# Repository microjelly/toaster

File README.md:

# toaster
A barebones toaster reflow board and software. For details please visit my [project log](https://microjelly.com/reflow-controller-replacement/)

## Software
### Build
This project currently is using a Docker based build system. 
\
\
*from a command line*
```bash
git clone https://github.com/microjelly/toaster.git
cd toaster/build
make sdcc/stm8s-ebake1.ihx
make sdcc/n76e003-ebake1.ihx
```
`stm8s-ebake1.ihx` and `n76e003-ebake1.ihx` will be found in the `build/bin` directory. 

### Flash STM8s
https://github.com/vdudouyt/stm8flash
```bash
stm8flash -c stlinkv2 -p stm8s103?3 -w stm8s-ebake1.ihx
```

### Flash N76E003
https://github.com/erincandescent/nuvoprog
```bash
nuvoprog program -t n76e003 -c FFFFFFFF -a n76e003-bake1.ihx
```

## Hardware
`hw/v1/bom/index.html` has component value and placement information.

### STM8s build
Reference | Value
-- | --
C5 | 1uF
R5 | DNP (Do Not Populate)
U1 | STM8S103F3P6

### N76E003 build
Reference | Value
-- | --
C5 | DNP (Do Not Populate)
R5 | 0 Ohm
U1 | N76E003AT20

### Programing/Debug Header
The header uses a 10pin card edge 2.54mm pitch connector.
```
Top with pads on the bottom right
 | 2| 4| 6| 8|10|

Bottom with pads on the bottom left
 | 1| 3| 5| 7| 9|
```

Pad | STM8s | N76E003
-- | -- | --
1 | 3v3 | 3v3
2 | 3v3 | 3v3
3 | GND | GND
4 | SWIM | ICPCK
5 | GND | GND
6 | GND | GND
7 | RX | RX
8 | NRST | RST
9 | TX | TX
10 | N/A | ICPDAT

## Debug
Connect RX/TX/GND to a serial device.
\
\
OSX; (exit Ctrl+A; Ctrl+\\; Y)
```bash
screen -port /dev/tty.usbserial-0001 115200
```

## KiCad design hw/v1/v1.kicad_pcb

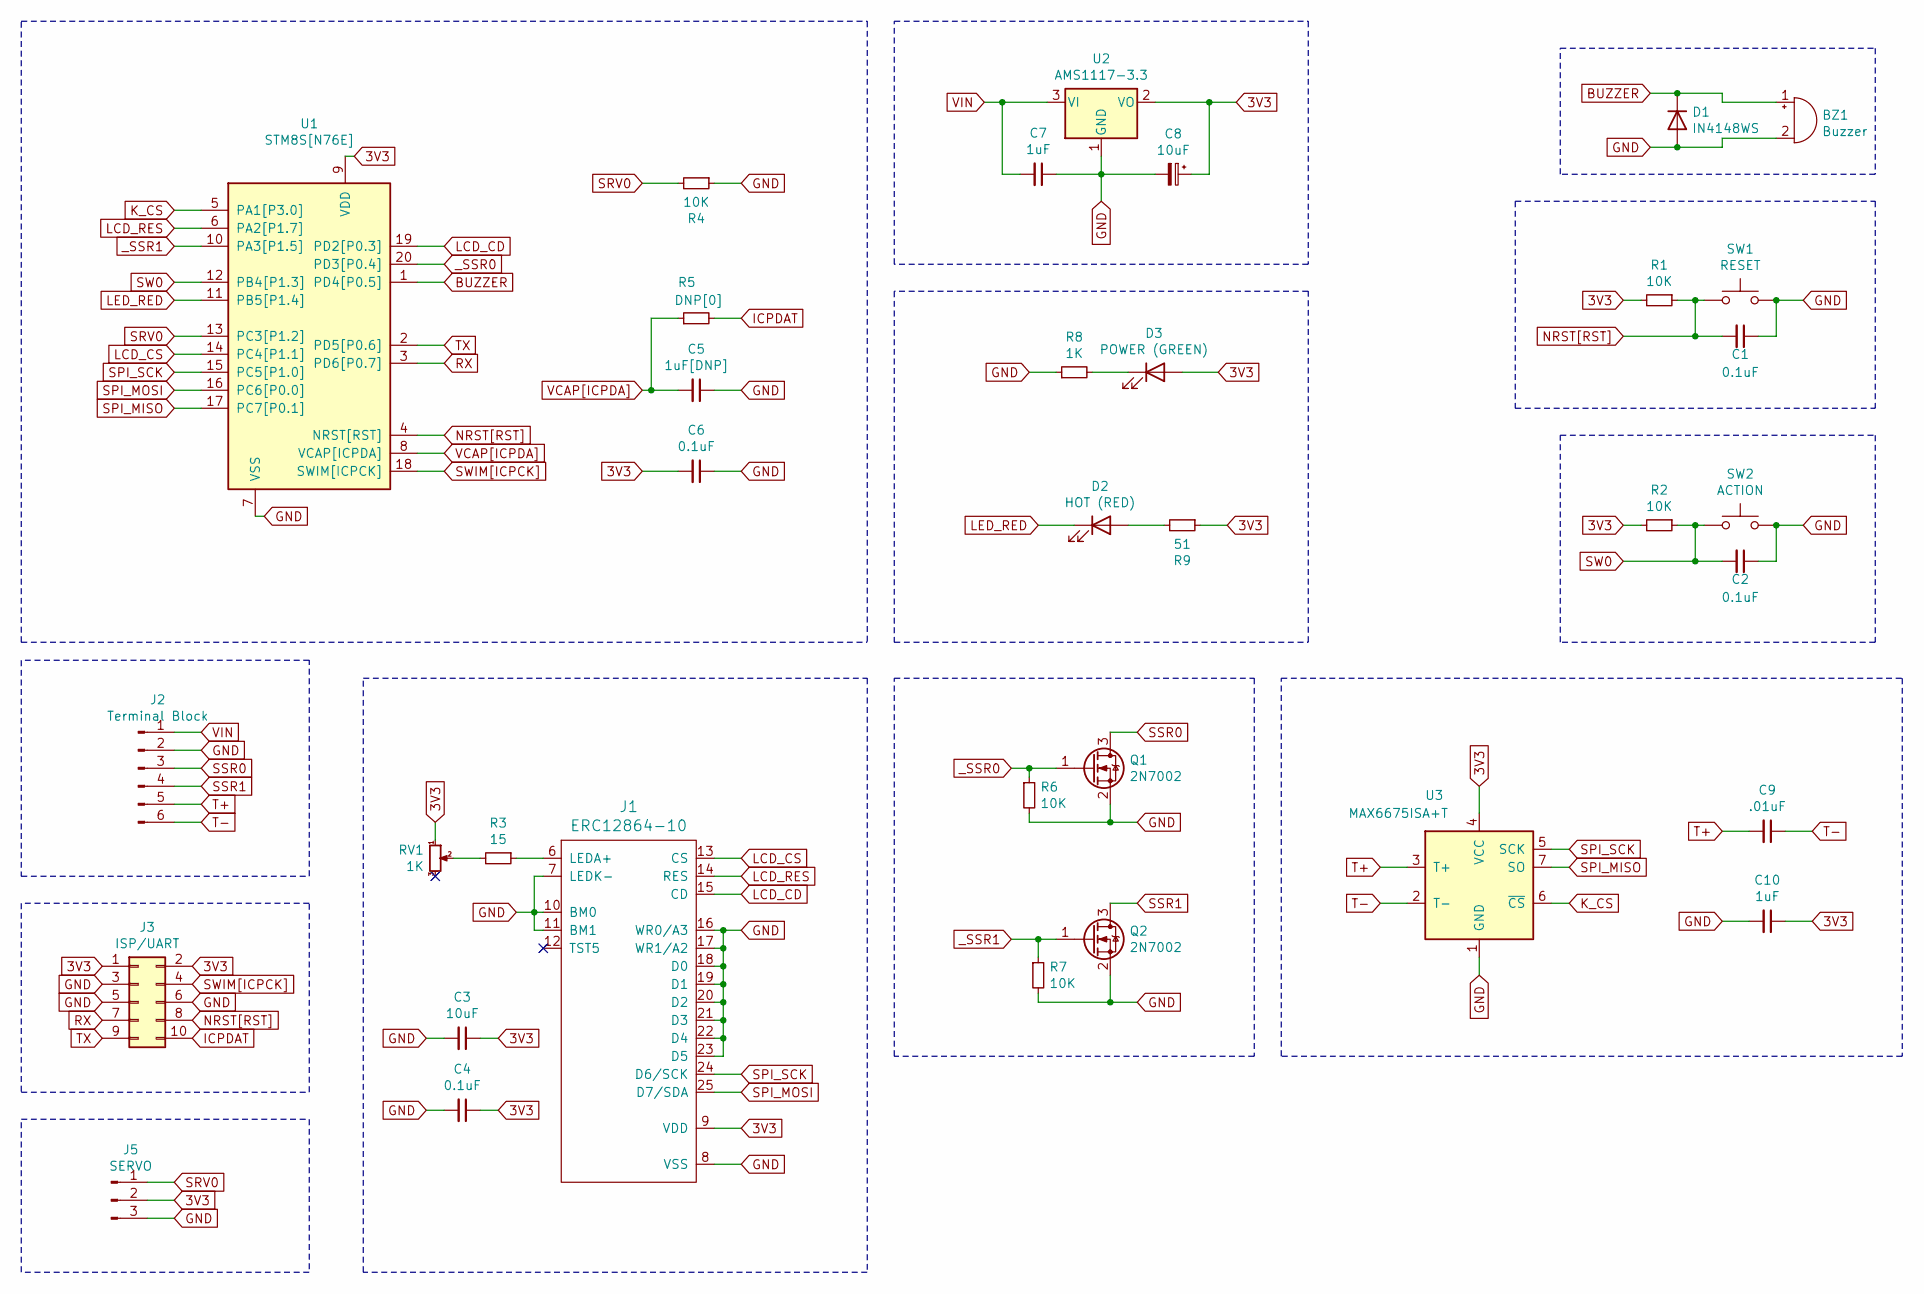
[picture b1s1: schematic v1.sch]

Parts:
BZ1: Buzzer; MLT-8530
C1, C2, C4, C6: 0.1uF; C_0805_2012Metric
C3: 10uF; C_0805_2012Metric
C5: 1uF[DNP]; C_0805_2012Metric
C7, C10: 1uF; C_0805_2012Metric
C8: 10uF; CP_EIA-3216-18_Kemet-A
C9: .01uF; C_0805_2012Metric
D1: IN4148WS; D_SOD-323
D2: HOT (RED); LED_0805_2012Metric
D3: POWER (GREEN); LED_0805_2012Metric
J1: ERC12864-10; ER-CON30HB-1
J2: Terminal Block; HT396V-3.96-6p
J3: ISP/UART; TRUDEAU_C2X5_SMD
J5: SERVO; PinHeader_1x03_P2.54mm_Vertical
Q1, Q2: 2N7002; SOT-23
R1, R2, R4, R6, R7: 10K; R_0805_2012Metric
R3: 15; R_0805_2012Metric
R5: DNP[0]; R_0805_2012Metric
R8: 1K; R_0805_2012Metric
R9: 51; R_0805_2012Metric
RV1: 1K; Potentiometer_Bourns_TC33X_Vertical
SW1: RESET; TS-1186D-C-A
SW2: ACTION; UK-B0229-G2.5-B-250
U1: STM8S[N76E]; TSSOP-20_4.4x6.5mm_P0.65mm
U2: AMS1117-3.3; SOT-223-3_TabPin2
U3: MAX6675ISA+T; SOIC-8_3.9x4.9mm_P1.27mm

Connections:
3V3: C3.1, C4.1, C6.2, C8.1, C10.1, D3.2 (A), J1.9 (VDD), J3.1, J3.2, J5.2, R1.2, R2.2, R9.1, RV1.1, U1.9 (VDD), U2.2 (VO), U3.4 (VCC)
BUZZER: BZ1.1 (-), D1.1 (K), U1.1 (PD4[P0.5])
GND: BZ1.2 (+), C1.1, C2.1, C3.2, C4.2, C5.1, C6.1, C7.1, C8.2, C10.2, D1.2 (A), J1.7 (LEDK-), J1.8 (VSS), J1.10 (BM0), J1.11 (BM1), J1.16 (WR0/A3), J1.17 (WR1/A2), J1.18 (D0), J1.19 (D1), J1.20 (D2), J1.21 (D3), J1.22 (D4), J1.23 (D5), J2.2, J3.3, J3.5, J3.6, J5.3, Q1.2 (S), Q2.2 (S), R4.1, R6.2, R7.2, R8.1, SW1.2, SW2.2, U1.7 (VSS), U2.1 (GND), U3.1 (GND)
ICPDAT: J3.10, R5.2
K_CS: U1.5 (PA1[P3.0]), U3.6 (~CS~)
LCD_CD: J1.15 (CD), U1.19 (PD2[P0.3])
LCD_CS: J1.13 (CS), U1.14 (PC4[P1.1])
LCD_RES: J1.14 (RES), U1.6 (PA2[P1.7])
LED_RED: D2.1 (K), U1.11 (PB5[P1.4])
NRST[RST]: C1.2, J3.8, R1.1, SW1.1, U1.4 (NRST[RST])
unnamed: D2.2 (A), R9.2
unnamed: D3.1 (K), R8.2
unnamed: J1.6 (LEDA+), R3.1
unnamed: R3.2, RV1.2
RX: J3.7, U1.3 (PD6[P0.7])
SPI_MISO: U1.17 (PC7[P0.1]), U3.7 (SO)
SPI_MOSI: J1.25 (D7/SDA), U1.16 (PC6[P0.0])
SPI_SCK: J1.24 (D6/SCK), U1.15 (PC5[P1.0]), U3.5 (SCK)
SRV0: J5.1, R4.2, U1.13 (PC3[P1.2])
SSR0: J2.3, Q1.3 (D)
SSR1: J2.4, Q2.3 (D)
SW0: C2.2, R2.1, SW2.1, U1.12 (PB4[P1.3])
SWIM[ICPCK]: J3.4, U1.18 (SWIM[ICPCK])
T+: C9.2, J2.5, U3.3 (T+)
T-: C9.1, J2.6, U3.2 (T-)
TX: J3.9, U1.2 (PD5[P0.6])
VCAP[ICPDA]: C5.2, R5.1, U1.8 (VCAP[ICPDA])
VIN: C7.2, J2.1, U2.3 (VI)
_SSR0: Q1.1 (G), R6.1, U1.20 (PD3[P0.4])
_SSR1: Q2.1 (G), R7.1, U1.10 (PA3[P1.5])

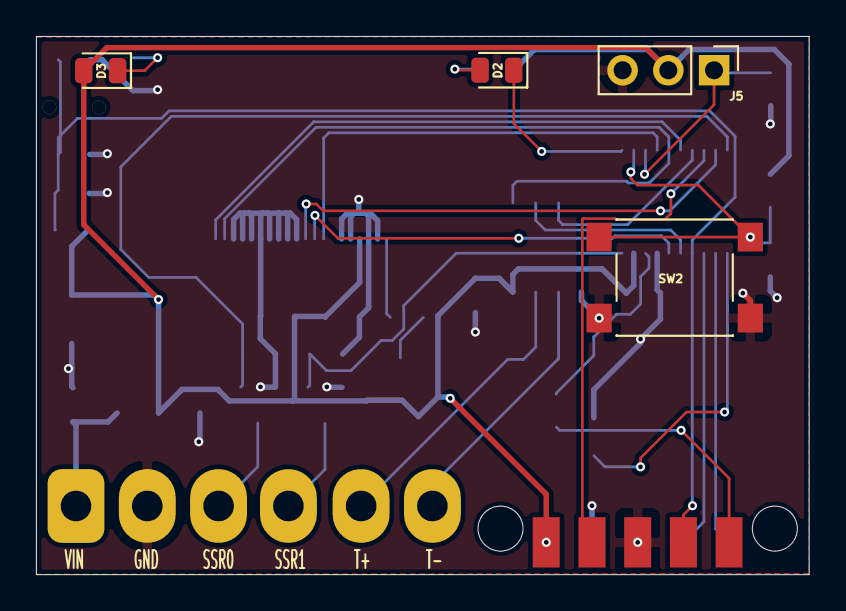
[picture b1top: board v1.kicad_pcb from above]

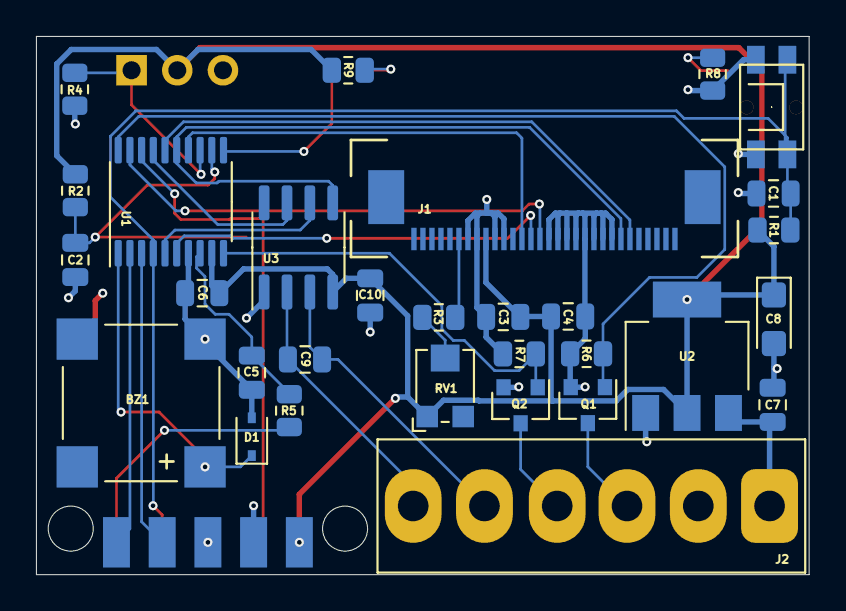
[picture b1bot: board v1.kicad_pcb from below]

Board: 2 copper layers, 42.9 x 29.9 mm, 35 parts (31 on the bottom side), 30 nets.

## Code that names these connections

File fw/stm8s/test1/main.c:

/*
 * STM8S-TOASTER
 *
 * LED
 *  LED0 -> PB5 (RED; HOT)
 * SSR
 *  SSR0 -> PD3 [tim2-ch2] > TOP
 *  SSR1 -> PA3 [tim2-ch3] > BOTTOM
 * SW
 *  SW0  -> PB4
 * OLED
 *  CS   -> PC4
 *  DC   -> PD2
 *  RES  -> PC3
 *  SCK  -> PC5 [spi]
 *  MOSI -> PC6 [spi]
 * MAX6675
 *  CS   -> PA1
 *  SCK  -> PC5 [spi]
 *  MISO -> PC7 [spi]
 * BEEP
 *  BEEP -> PD4
 * UART1
 *  TX   -> PD5
 *  RX   -> PD6
 */
#include <stdint.h>
#include <stdbool.h>
#include <stm8s.h>
#include <format.h>
#include <clock.h>
#include <uart_stdout.h>
#include <uart.h>
#include <lcd12864.h>
#include <max6675.h>
#include <beep.h>

#include "defaults.h"

/* TIM1 Update/Overflow interrupt handling routine */
static volatile uint16_t tim1Value;
void TIM1_update(void) __interrupt(TIM1_OVR_UIF_IRQ)
{
    tim1Value++;
    TIM1_SR1 &= ~TIM_SR1_UIF;
}

void setOutput(uint8_t value0, uint8_t value1)
{
    uint16_t ccr = ((PWM_CLK / PWM_FREQ) * value0) / 100;
    if (ccr > 0)
    {
        TIM2_CCR2H = ccr >> 8; // Start off
        TIM2_CCR2L = ccr & 0x00FF;
    }
    else
    {
        TIM2_CCR2H = 0;
        TIM2_CCR2L = 0;
    }
    ccr = ((PWM_CLK / PWM_FREQ) * value1) / 100;
    if (ccr > 0)
    {
        TIM2_CCR3H = ccr >> 8; // Start off
        TIM2_CCR3L = ccr & 0x00FF;
    }
    else
    {
        TIM2_CCR3H = 0;
        TIM2_CCR3L = 0;
    }
}

int main(void)
{
    volatile uint16_t previousTicks = 0xffff;
    volatile uint16_t previousSecond = 0xffff;
    volatile uint8_t beeps = 2;
    volatile bool beepOn = false;

    sim();
    clock_init();
    uart_init();
    max6675_init();
    beep_init();

    /* LED setup */
    PORT(LED0_PORT, DDR) |= LED0_PIN;
    PORT(LED0_PORT, CR1) |= LED0_PIN;

    /* TIM1 setup ~250ms */
    tim1Value = 0;
    TIM1_PSCRH = 0x10;
    TIM1_PSCRL = 0x00;
    TIM1_ARRH = 0x03;
    TIM1_ARRL = 0xd0;
    TIM1_IER |= TIM_IER_UIE;
    TIM1_CR1 |= TIM_CR1_CEN;

    /* TIM2/PWM setup */
    TIM2_PSCR = PWM_PSCR;
    TIM2_ARRH = PWM_ARR >> 8;
    TIM2_ARRL = PWM_ARR & 0x00FF;
    PORT(SSR0_PORT, DDR) |= SSR0_PIN;
    PORT(SSR0_PORT, CR1) |= SSR0_PIN;
    TIM2_CCER1 |= TIM2_CCER1_CC2E;
    TIM2_CCMR2 |= (TIM2_CCMR2_OC2M1 | TIM2_CCMR2_OC2M2);
    TIM2_CCMR2 &= ~TIM2_CCMR2_OC2M0;
    TIM2_CCR2H = 0;
    TIM2_CCR2L = 0;
    PORT(SSR1_PORT, DDR) |= SSR1_PIN;
    PORT(SSR1_PORT, CR1) |= SSR1_PIN;
    TIM2_CCER2 |= TIM2_CCER2_CC3E;
    TIM2_CCMR3 |= (TIM2_CCMR2_OC2M1 | TIM2_CCMR2_OC2M2);
    TIM2_CCMR3 &= ~TIM2_CCMR2_OC2M0;
    TIM2_CCR3H = 0;
    TIM2_CCR3L = 0;
    TIM2_CR1 |= TIM2_CR1_CEN;

    rim();
    
    putstring("\r\nTEST1\r\n\r\n");
    setOutput(25, 50);
    
    lcd12864_init(true);
    struct LCD12864_SEGMENT *lcdTitle = lcd12864_new_segment(0, 1, 1, 1, 1, '#');
    struct LCD12864_SEGMENT *lcdTime = lcd12864_new_segment(1, 2, 2, 1, 1, ' ');
    struct LCD12864_SEGMENT *lcdPowerTemp = lcd12864_new_segment(3, 2, 3, 1, 1, ' ');
    struct LCD12864_SEGMENT *lcdStatus = lcd12864_new_segment(6, 1, 2, 1, 1, '#');

    do
    {
        volatile uint16_t currentTicks = tim1Value;
        volatile uint16_t currentSecond = (currentTicks / 4);
        volatile bool isOneSecondInterval = false;

        if (previousTicks != currentTicks)
        {
            previousTicks = currentTicks;
            if (previousSecond != currentSecond)
            {
                previousSecond = currentSecond;
                isOneSecondInterval = true;
            }
            if (beeps)
            {
                if ((currentTicks % 2) == 0)
                {
                    beep_on();
                    PORT(LED0_PORT, ODR) &= ~LED0_PIN;
                    beepOn = true;
                }
                else if (beepOn)
                {
                    beep_off();
                    PORT(LED0_PORT, ODR) |= LED0_PIN;
                    beepOn = false;
                    beeps--;
                }
            }
        }

        if (isOneSecondInterval)
        {
            
            uint16_t dT = currentSecond;
            volatile uint16_t currentTemperatureRaw = max6675_read();
            volatile uint16_t currentTemperature = currentTemperatureRaw / 4;
            volatile uint16_t currentTemperaturePoint = (currentTemperatureRaw - (currentTemperature * 4)) * 100;
            uint16_t lm = (dT / 60);
            uint16_t tm = (lm % 60);
            uint8_t th = (lm / 60);
            uint8_t ts = (dT % 60);

            format_sprintf(lcdTime->buffer, "? %02u:%02u:%02u", th, tm, ts);
            format_sprintf(lcdPowerTemp->buffer, "--:-- %3u C", currentTemperature);

            uint8_t *ptr = lcdTime->buffer;
            putstring(ptr);
            putstring(" ");
            ptr = lcdPowerTemp->buffer;
            putstring(ptr);
            putstring("\r\n");

            lcd12864_display_segment(lcdTitle);
            lcd12864_display_segment(lcdTime);
            lcd12864_display_segment(lcdPowerTemp);
            lcd12864_display_segment(lcdStatus);
        }

        wfi();
    } while (1);
}

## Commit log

2020-08-22 first push
2021-01-21 lcd+
2021-01-21 rm hw; plan to add kicad files after next rev
2021-02-02 rebuild repo
2021-02-23 +bias/fix lcd flip
2021-08-12 fix bias
2021-08-13 readme updates
2021-08-13 adn/and
2021-08-13 ignore
2021-08-14 v1 hw/fw
2021-08-17 doc cleanup
2021-09-15 fix stm8s-ebake1 for hw v1
